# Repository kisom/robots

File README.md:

# Robots

I like building robots. This is PlatformIO code for the non-ROS robots.

* [Scooter](https://hackaday.io/project/166550-scooter) is a 2WD robot
  with an array of ultrasonic ranging sensors. It's an experiment in
  obstacle avoidance. It's since been scrapped.
* [Scooter 2](https://hackaday.io/project/166747-scooter-2) replaces
  Scooter to do the same things with a different but very similar chassis.

Other robots:

* [krex](https://hackaday.io/project/166400-krex) is a ROS robot based
  on the Jetson Nano; source is in the [krex-ros](https://github.com/kisom/krex-ros)
  repository.

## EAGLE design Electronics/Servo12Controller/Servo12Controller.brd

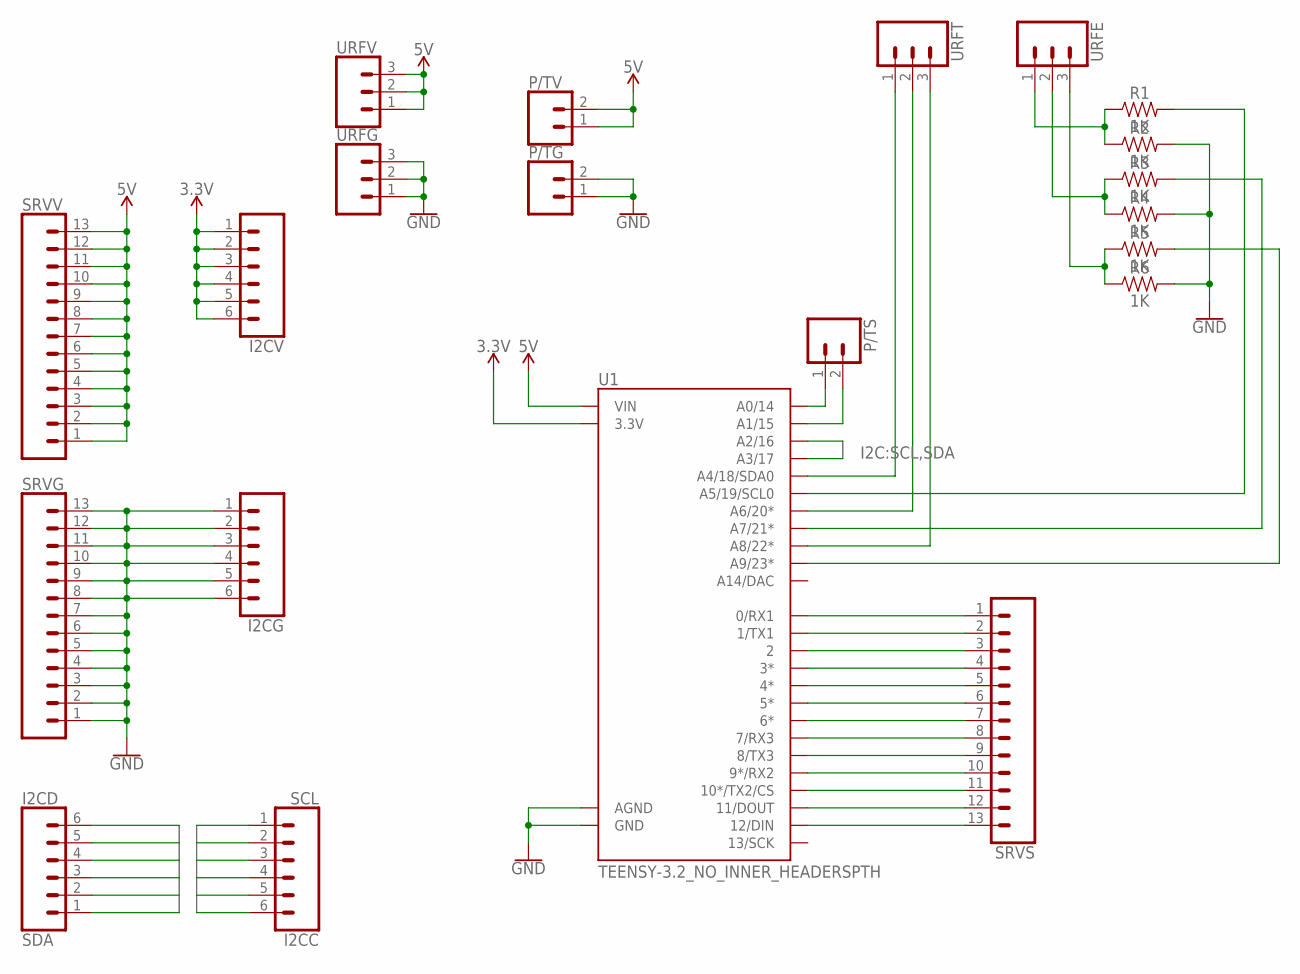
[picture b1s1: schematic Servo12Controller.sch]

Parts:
I2CC: SCL; 1X06_LOCK
I2CD: SDA; 1X06_LOCK
I2CG, I2CV: CONN_06LOCK; 1X06_LOCK
P/TG: CONN_02LOCK; 1X02_LOCK
P/TS: CONN_02LOCK; 1X02_LOCK
P/TV: CONN_02LOCK; 1X02_LOCK
R1, R2, R3, R4, R5, R6: 1K; AXIAL-0.3
SRVG: CONN_13LOCK; 1X13_LOCK
SRVS: CONN_13LOCK; 1X13_LOCK
SRVV: CONN_13LOCK; 1X13_LOCK
U1: TEENSY-3.2_NO_INNER_HEADERSPTH; TEENSY_TEENSY-3.2-PTH
URFE: CONN_03LOCK; 1X03_LOCK
URFG: CONN_03LOCK; 1X03_LOCK
URFT: CONN_03LOCK; 1X03_LOCK
URFV: CONN_03LOCK; 1X03_LOCK

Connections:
3.3V: I2CV.1, I2CV.2, I2CV.3, I2CV.4, I2CV.5, I2CV.6, U1.3.3V, U1.3.3V-1 (3.3V)
5V: P/TV.1, P/TV.2, SRVV.1, SRVV.2, SRVV.3, SRVV.4, SRVV.5, SRVV.6, SRVV.7, SRVV.8, SRVV.9, SRVV.10, SRVV.11, SRVV.12, SRVV.13, U1.VIN, URFV.1, URFV.2, URFV.3
GND: I2CG.1, I2CG.2, I2CG.3, I2CG.4, I2CG.5, I2CG.6, P/TG.1, P/TG.2, R2.P$2 (2), R4.P$2 (2), R6.P$2 (2), SRVG.1, SRVG.2, SRVG.3, SRVG.4, SRVG.5, SRVG.6, SRVG.7, SRVG.8, SRVG.9, SRVG.10, SRVG.11, SRVG.12, SRVG.13, U1.AGND, U1.GND, U1.GND1 (GND), URFG.1, URFG.2, URFG.3
unnamed: SRVS.1, U1.0 (0/RX1)
unnamed: SRVS.2, U1.1 (1/TX1)
unnamed: SRVS.3, U1.2
unnamed: SRVS.4, U1.3 (3*)
unnamed: SRVS.5, U1.4 (4*)
unnamed: SRVS.6, U1.5 (5*)
unnamed: SRVS.7, U1.6 (6*)
unnamed: SRVS.8, U1.7 (7/RX3)
unnamed: SRVS.9, U1.8 (8/TX3)
unnamed: SRVS.10, U1.9 (9*/RX2)
unnamed: SRVS.11, U1.10 (10*/TX2/CS)
unnamed: SRVS.12, U1.11 (11/DOUT)
unnamed: SRVS.13, U1.12 (12/DIN)
unnamed: U1.18 (A4/18/SDA0), URFT.1
unnamed: U1.20 (A6/20*), URFT.2
unnamed: U1.22 (A8/22*), URFT.3
unnamed: R1.P$2 (2), U1.19 (A5/19/SCL0)
unnamed: R3.P$2 (2), U1.21 (A7/21*)
unnamed: R5.P$2 (2), U1.23 (A9/23*)
unnamed: P/TS.1, U1.14 (A0/14)
unnamed: P/TS.2, U1.15 (A1/15)
unnamed: R1.P$1 (1), R2.P$1 (1), URFE.1
unnamed: R3.P$1 (1), R4.P$1 (1), URFE.2
unnamed: R5.P$1 (1), R6.P$1 (1), URFE.3
SCL: I2CC.1, I2CC.2, I2CC.3, I2CC.4, I2CC.5, I2CC.6, U1.16 (A2/16)
SDA: I2CD.1, I2CD.2, I2CD.3, I2CD.4, I2CD.5, I2CD.6, U1.17 (A3/17)

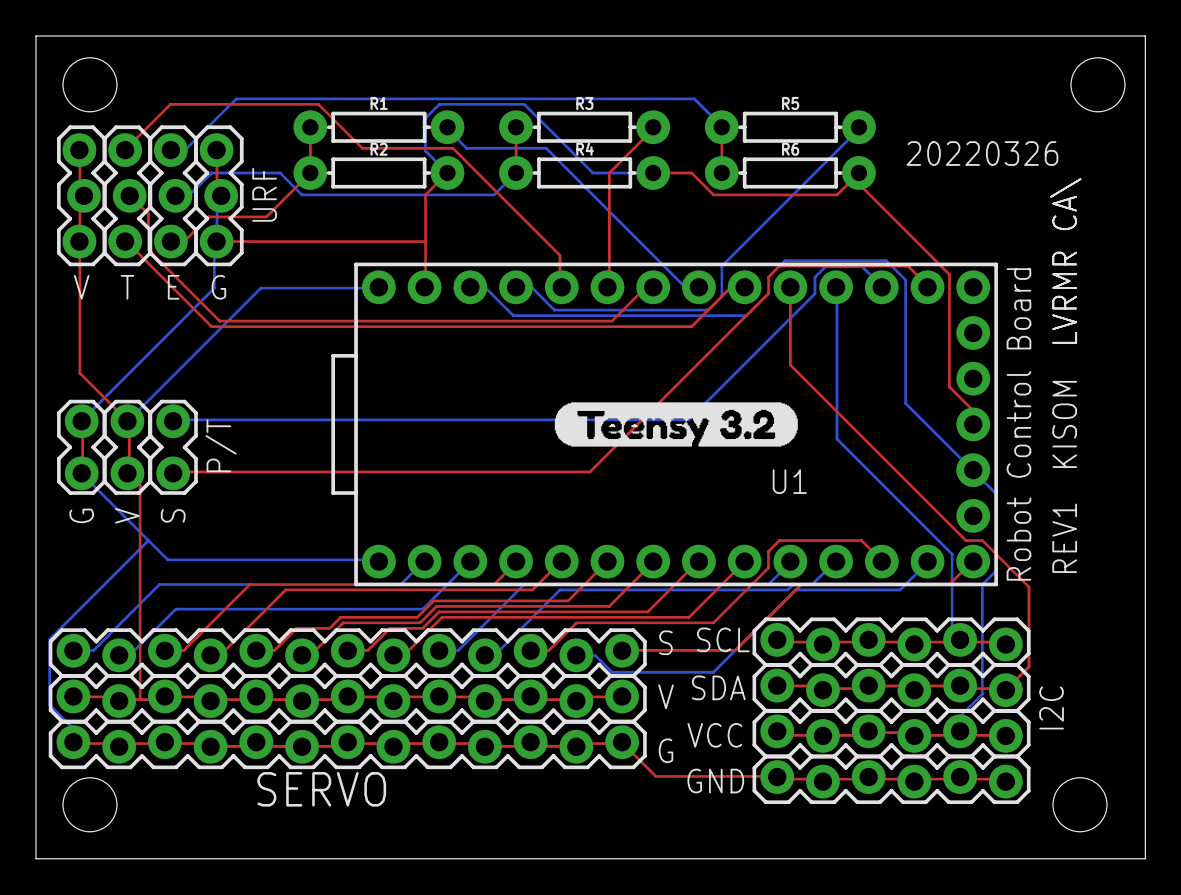
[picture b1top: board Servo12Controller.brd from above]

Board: 2 copper layers, 61.6 x 45.7 mm, 21 parts (0 on the bottom side), 29 nets.

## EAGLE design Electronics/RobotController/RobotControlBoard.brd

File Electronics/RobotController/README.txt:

RobotController
==============

This is a Teensy-based robot controller, particularly designed as
a co-proceessor for Pololu's A-Star 32U4-based robots or in conjunction
with a Raspberry Pi.

Pinouts
=======

Pin		Function		Description
-----------------------------------------------------------------------------
0		RX			FTDI RX
1		TX			FTDI TX
2					URS 0 Trigger
3					URS 1 Trigger
4					URS 2 Trigger
5					URS 3 Trigger
6					URS 4 Trigger
7					URS 0 Echo
8					URS 1 Echo
9					URS 2 Echo
10					URS 3 Echo
11					URS 4 Echo
12					I/O 0
13					I/O 1
14					Sensor 0
15					Sensor 1
16					Sensor 2
17					Sensor 3
18					I2C SDA
19					I2C SCL
20					Sensor 4
21					Sensor 5
22					Sensor 6
23					Sensor 7

The power select pins are designed to support 3.3V and 5V
power input. Add a jumper across to the appropriate port
and run the power input to the unused PWRSEL pin. If Vcc
is 3.3V and 5V is needed as well, connect 5V to the 5V
power supply.

The FTDI so					Sensor 7

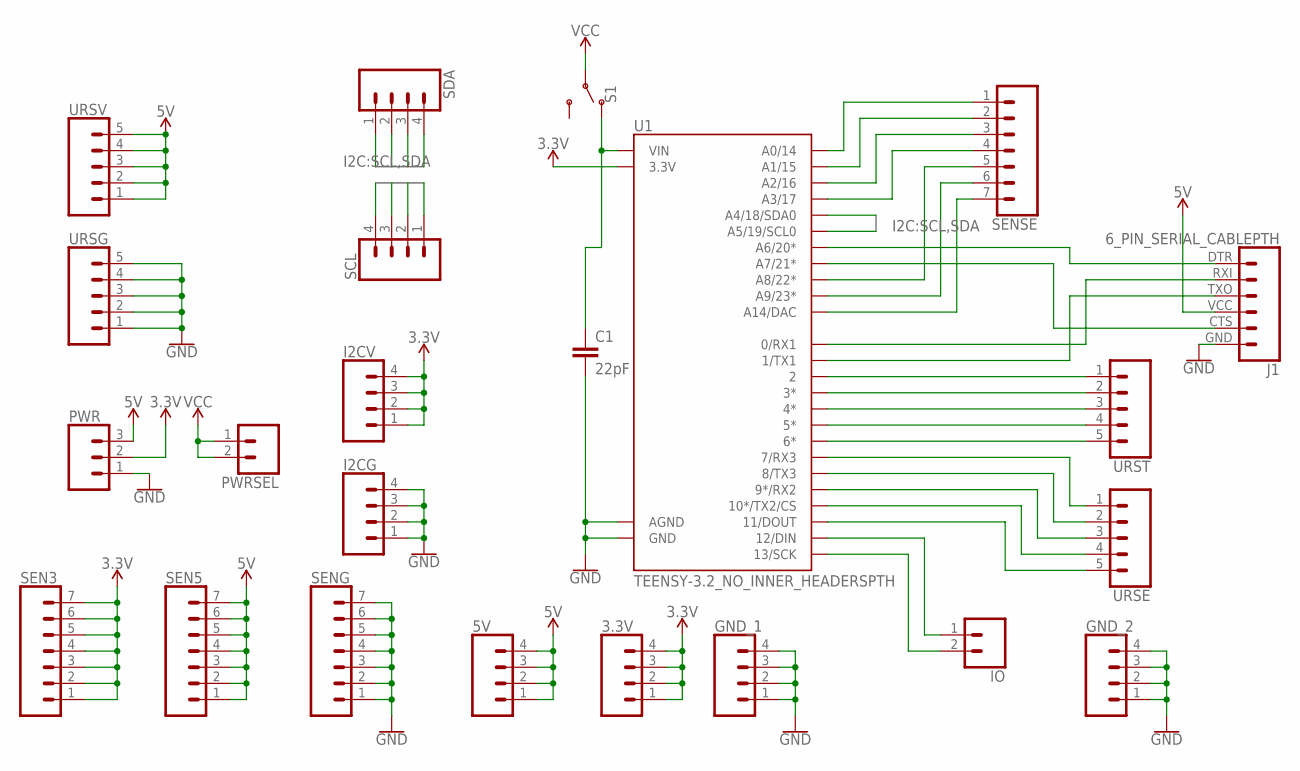
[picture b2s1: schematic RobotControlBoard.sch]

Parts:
3.3V, 5V: CONN_04LOCK; 1X04_LOCK
C1: 22pF; CAP-PTH-2.54
GND_1, GND_2: CONN_04LOCK; 1X04_LOCK
I2CG, I2CV: CONN_04LOCK; 1X04_LOCK
IO: CONN_02LOCK; 1X02_LOCK
J1: 6_PIN_SERIAL_CABLEPTH; FTDI_BASIC
PWR: CONN_03LOCK; 1X03_LOCK
PWRSEL: CONN_02LOCK; 1X02_LOCK
S1: SWITCH-SPDT-PTH-11.6X4.0MM-LOCK; SWITCH_SPDT_PTH_11.6X4.0MM_LOCK
SCL: CONN_04LOCK; 1X04_LOCK
SDA: CONN_04LOCK; 1X04_LOCK
SEN3, SEN5: CONN_07LOCK; 1X07_LOCK
SENG: CONN_07LOCK; 1X07_LOCK
SENSE: CONN_07LOCK; 1X07_LOCK
U1: TEENSY-3.2_NO_INNER_HEADERSPTH; TEENSY_TEENSY-3.2-PTH
URSE: CONN_05LOCK; 1X05_LOCK
URSG: CONN_05LOCK; 1X05_LOCK
URST: CONN_05LOCK; 1X05_LOCK
URSV: CONN_05LOCK; 1X05_LOCK

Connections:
3.3V: 3.3V.1, 3.3V.2, 3.3V.3, 3.3V.4, I2CV.1, I2CV.2, I2CV.3, I2CV.4, PWR.2, SEN3.1, SEN3.2, SEN3.3, SEN3.4, SEN3.5, SEN3.6, SEN3.7, U1.3.3V, U1.3.3V-1 (3.3V)
5V: 5V.1, 5V.2, 5V.3, 5V.4, J1.VCC (4), PWR.3, SEN5.1, SEN5.2, SEN5.3, SEN5.4, SEN5.5, SEN5.6, SEN5.7, URSV.1, URSV.2, URSV.3, URSV.4, URSV.5
GND: C1.2, GND_1.1, GND_1.2, GND_1.3, GND_1.4, GND_2.1, GND_2.2, GND_2.3, GND_2.4, I2CG.1, I2CG.2, I2CG.3, I2CG.4, J1.GND (6), PWR.1, SENG.1, SENG.2, SENG.3, SENG.4, SENG.5, SENG.6, SENG.7, U1.AGND, U1.GND, U1.GND1 (GND), URSG.1, URSG.2, URSG.3, URSG.4, URSG.5
unnamed: U1.2, URST.1
unnamed: U1.3 (3*), URST.2
unnamed: U1.4 (4*), URST.3
unnamed: U1.5 (5*), URST.4
unnamed: U1.6 (6*), URST.5
unnamed: U1.7 (7/RX3), URSE.1
unnamed: U1.8 (8/TX3), URSE.2
unnamed: U1.9 (9*/RX2), URSE.3
unnamed: U1.10 (10*/TX2/CS), URSE.4
unnamed: U1.11 (11/DOUT), URSE.5
unnamed: J1.RXI (2), U1.0 (0/RX1)
unnamed: J1.TXO (3), U1.1 (1/TX1)
unnamed: SENSE.1, U1.14 (A0/14)
unnamed: SENSE.2, U1.15 (A1/15)
unnamed: SENSE.3, U1.16 (A2/16)
unnamed: SENSE.4, U1.17 (A3/17)
unnamed: J1.DTR (1), U1.20 (A6/20*)
unnamed: J1.CTS (5), U1.21 (A7/21*)
unnamed: SENSE.5, U1.22 (A8/22*)
unnamed: SENSE.6, U1.23 (A9/23*)
unnamed: SENSE.7, U1.A14/DAC
unnamed: C1.1, S1.1 (O), U1.VIN
unnamed: IO.1, U1.12 (12/DIN)
unnamed: IO.2, U1.13 (13/SCK)
SCL: SCL.1, SCL.2, SCL.3, SCL.4, U1.19 (A5/19/SCL0)
SDA: SDA.1, SDA.2, SDA.3, SDA.4, U1.18 (A4/18/SDA0)
VCC: PWRSEL.1, PWRSEL.2, S1.2

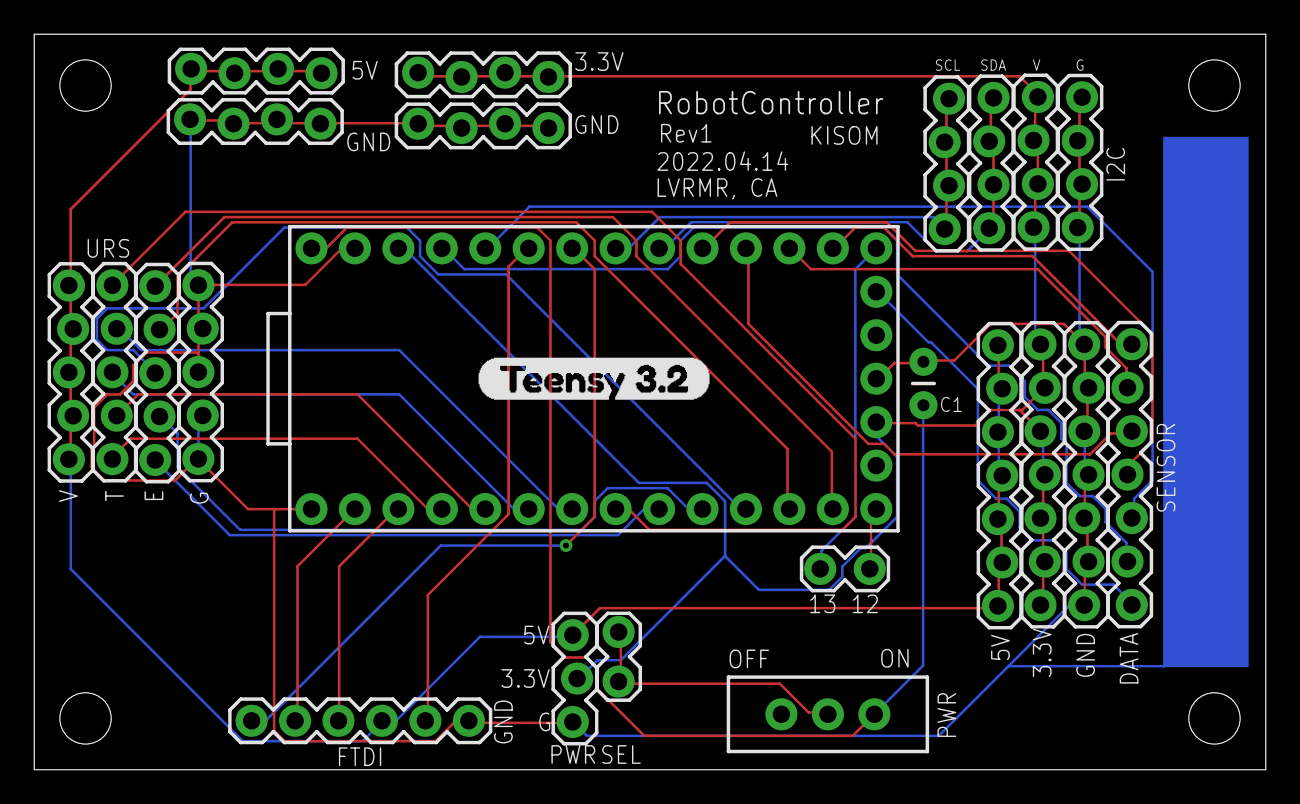
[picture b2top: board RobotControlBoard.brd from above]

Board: 2 copper layers, 72.0 x 43.0 mm, 23 parts (0 on the bottom side), 30 nets.

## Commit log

2019-07-13 inital import
2019-07-13 Vendor SCMD, code fixups.
2019-07-13 Adding license and readmes.
2019-07-13 Add link to krex.
2019-07-13 Add HC-SR04 test sketch.
2019-07-13 Add ping))) test sketch.
2019-07-13 Rewire some things.
2019-07-13 Add hwtest README.
2019-07-22 scooter: enable motor disabling.
2019-07-24 Start work on Sedan.
2019-07-24 Add todo for sedan.
2019-07-24 sedan: Refactor motor control out.
2019-07-24 Sedan -> scooter2.
2019-07-24 Start refactoring URS code.
2019-07-24 URS work.
2019-07-25 Verified HCSR04 lib works.
2019-07-26 scooter2: switch URS->floats to save memory.
2019-07-26 Add support for RBT.
2019-07-26 Experiment results.
2019-07-26 Add and verify single-pin HCSR04.
2019-07-26 Add clion config.
2019-07-26 Rename HCSR04_Single -> HCSR04SinglePin.
2019-07-26 Move HCSR04 stuff into a lib.
2019-07-26 Let's see if this works.
2019-07-26 Some docs.
2019-07-26 Update README with scooter2.
2019-07-27 scooter2 now has a single panning HCSR04.
2019-07-27 Add logging and whatnot.
2019-07-29 Moving things around, need to debug.
2022-04-08 Starting work on the 3Pi+.
2022-04-08 movitating some things
2022-04-08 renaming some stuff
2022-04-09 Add wntrmute OpenSCAD library
2022-04-09 updating 3Pi software and CAD files.
2022-04-09 move VURS bracket to main hardware area.
2022-04-09 dumb robot bounces around and hopefully doesn't die
2022-04-10 wntrmute.scad: actually use height parameter
2022-04-10 Add horizontal URS bracket.
2022-04-10 Add README.
2022-04-12 Add Romi hardware.
2022-04-18 Adding Teensy-based robot control board.
2022-04-18 Add servo-controller board.
2022-04-19 start Zumo code
2022-04-20 basic obstacle avoidance with the Zumo
2022-04-21 Zumo: adding differential encoder class.

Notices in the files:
parts and their libraries:
SparkFun-Capacitors: Licensing: Creative Commons ShareAlike 4.0 International - https://creativecommons.org/licenses/by-sa/4.0
